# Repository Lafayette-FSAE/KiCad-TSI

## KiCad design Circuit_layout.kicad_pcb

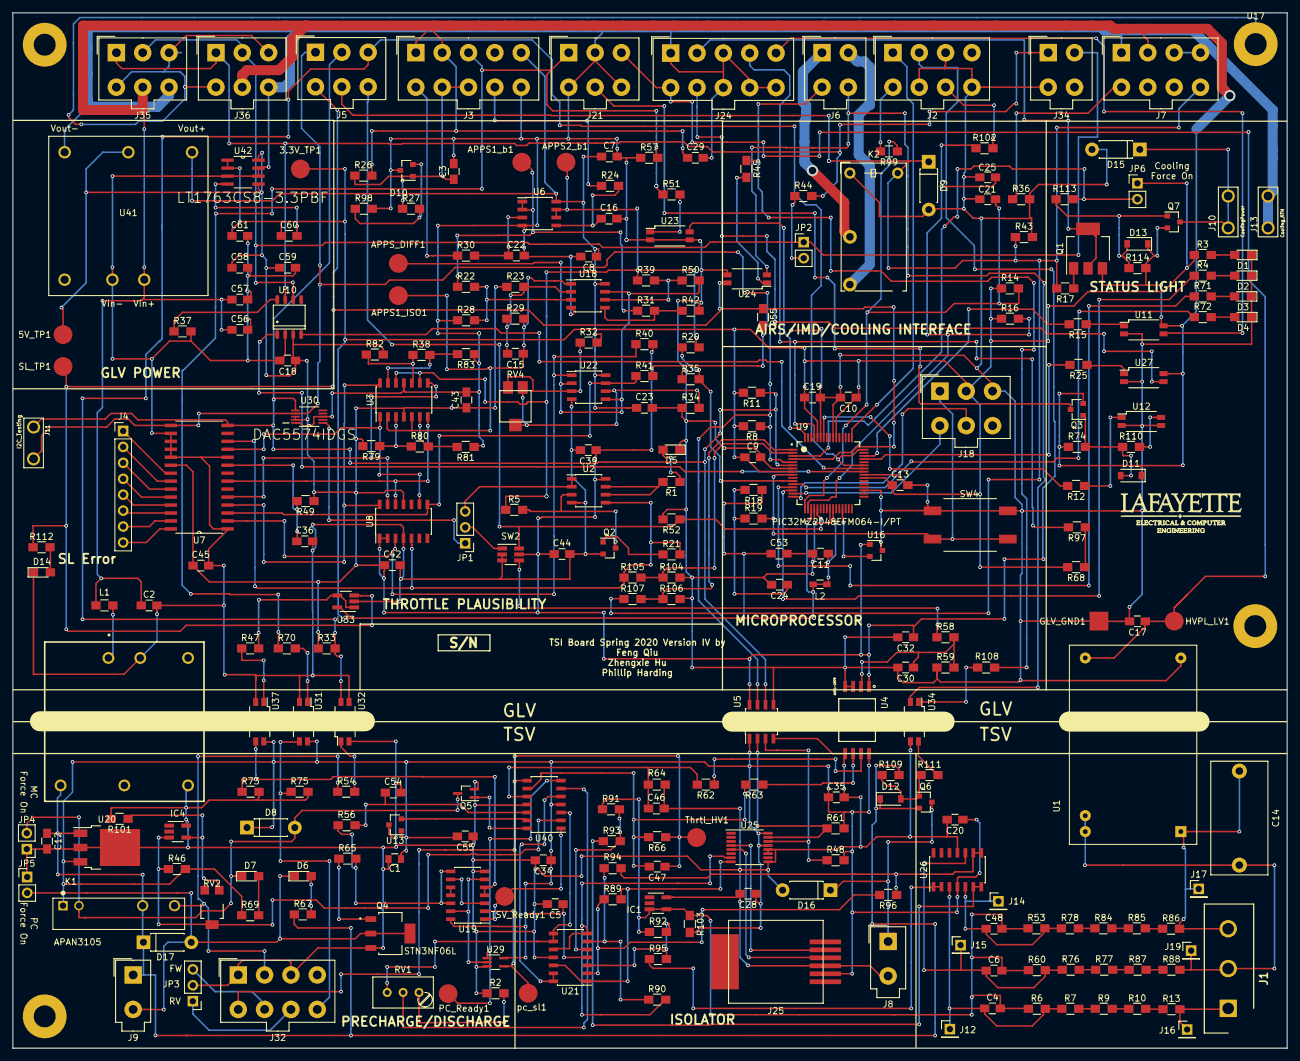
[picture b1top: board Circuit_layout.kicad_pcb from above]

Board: 2 copper layers, 203.2 x 165.1 mm, 281 parts (0 on the bottom side), 185 nets.

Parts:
3.3V_TP1: 3.3V_TP; Measurement_Point_Round-SMD-Pad_Big
5V_TP1: 5V_TP; Measurement_Point_Round-SMD-Pad_Big
APPS1_ISO1: APPS1_ISO; Measurement_Point_Round-SMD-Pad_Big
APPS1_b1: APPS1_b; Measurement_Point_Round-SMD-Pad_Big
APPS2_b1: APPS2_b; Measurement_Point_Round-SMD-Pad_Big
APPS_DIFF1: APPS_DIFF; Measurement_Point_Round-SMD-Pad_Big
C1: 0.47u; C_0805
C2, C17: 4.7u; C_0805_HandSoldering
C3, C5, C7, C8, C9, C10, C11, C13, C15, C16, C18, C19, C20, C21, C22, C23, C25, C28, C29, C32, C34, C35, C39, C42, C43, C44, C45, C53, C55, C58: 0.1u; C_0805_HandSoldering
C4, C6, C30, C46, C47, C48: 100p; C_0805_HandSoldering
C12: 0.33u; C_0805_HandSoldering
C14: 1u; C_Rect_L18.0mm_W9.0mm_P15.00mm_FKS3_FKP3
C24: 0.1uF; C_0805_HandSoldering
C36: 33p; C_0805_HandSoldering
C54: 15u; C_0805_HandSoldering
C56, C57, C61: 10u; C_0805_HandSoldering
C59, C60: 1u; C_0805_HandSoldering
D1: Power; LED_0805_HandSoldering
D2: Heartbeat; LED_0805_HandSoldering
D3: Spare/Fault; LED_0805_HandSoldering
D4: Spare; LED_0805_HandSoldering
D5: Throttle_PL; LED_0805_HandSoldering
D6, D7: LED; LED_0805_HandSoldering
D8, D9, D15, D16, D17: 1N4001; D_DO-41_SOD81_P7.62mm_Horizontal
D10: ATL431; SOT-23_D10_special
D11, D12, D13: MMSZ5231B-7-F; D_SOD-123
D14: SL Error; LED_0805_HandSoldering
GLV_GND1: GLV_GND; Measurement_Point_Square-SMD-Pad_Big
HVPL_LV1: TSAL_LV; Measurement_Point_Round-SMD-Pad_Big
IC1, IC4: TS431ILT; SOT-23-5_HandSoldering
J1: TSV; SHDR3W166P0X635_1X3_2032X762X1422P
J2: CoolingSystem; Molex_MiniFit-JR-5556-08A_2x04x4.20mm_Straight
J3: Pedal; Molex_MiniFit-JR-5556-10A_2x05x4.20mm_Straight
J4: Conn_01x08; Pin_Header_Straight_1x08_Pitch2.54mm
J5: Testing Connector; Molex_MiniFit-JR-5556-06A_2x03x4.20mm_Straight
J6: AIRs/SafetyLoop; Molex_MiniFit-JR-5556-04A_2x02x4.20mm_Straight
J7: IMD; Molex_MiniFit-JR-5556-08A_2x04x4.20mm_Straight
J8: DC_Relay; Molex_MiniFit-JR-5556-02A_2x01x4.20mm_Straight
J9: PC_Relay; Molex_MiniFit-JR-5556-02A_2x01x4.20mm_Straight
J10: CoolingPower; TE_1217861-1
J11: I2C_Testing; TE_1217861-1
J12, J14, J15, J16, J17, J19: Conn_01x01; Pin_Header_Straight_1x01_Pitch2.54mm
J13: Cooling_RTN; TE_1217861-1
J18: ICSP; Molex_MiniFit-JR-5556-06A_2x03x4.20mm_Straight
J21: Lights On Car; Molex_MiniFit-JR-5556-06A_2x03x4.20mm_Straight
J24: Cockpit; Molex_MiniFit-JR-5556-10A_2x05x4.20mm_Straight
J25: RJ11; MOLEX_RJ11
J32: Conn_MC; Molex_MiniFit-JR-5556-08A_2x04x4.20mm_Straight
J34: Can_Iso; Molex_MiniFit-JR-5556-04A_2x02x4.20mm_Straight
J35: GLV_In; Molex_MiniFit-JR-5556-06A_2x03x4.20mm_Straight
J36: GLV_Out; Molex_MiniFit-JR-5556-06A_2x03x4.20mm_Straight
JP1, JP3: Jumper_NC_Dual; Pin_Header_Straight_1x03_Pitch2.54mm
JP2, JP6: Jumper; Pin_Header_Straight_1x02_Pitch2.54mm
JP4, JP5: Jumper-Device; Pin_Header_Straight_1x02_Pitch2.54mm
K1: APAN3105; RELAY_APAN3105
K2: G6B-1174P-US-DC24; Relay_SPST_Finder_32.21-x300_special
L1: 2.2uH; L_0805_HandSoldering
L2: 28nH; L_0603_HandSoldering
PC_Ready1: Precharge_Ready; Measurement_Point_Round-SMD-Pad_Big
PS1: THN_30-2415WI; THN_30
Q1: ZVP0545G; SOT-223-3_TabPin2
Q2: MMBF170; SOT-23
Q3, Q6, Q7: ZVP1320F; SOT-23
Q4: STN3NF06L; SOT230P700X180-4N-speical
Q5: SI1302DL-T1-E3; SOT-323_SC-70_Handsoldering_special
R1, R47, R69, R105, R106: 500; R_0805_HandSoldering
R2: 95k; R_0805_HandSoldering
R3, R4, R71, R72, R112: 330; R_0805_HandSoldering
R5, R6, R8, R11, R14, R16, R17, R18, R21, R22, R23, R28, R29, R31, R39, R40, R41, R42, R48, R50, R52, R53, R59, R60, R61, R62, R63, R68, R89, R90, R91, R92, R93, R94, R95, R96, R97, R101, R110, R111, R113: 10k; R_0805_HandSoldering
R7, R9, R10, R13, R76, R77, R78, R84, R85, R86, R87, R88: 150k; R_0805_HandSoldering
R12, R15, R25: 300; R_0805_HandSoldering
R19, R37, R46, R103, R104: 1k; R_0805_HandSoldering
R20: 2k; R_0805_HandSoldering
R24, R30, R57: 100k; R_0805_HandSoldering
R26: 1K; R_0805_HandSoldering
R27, R98: 10K; R_0805_HandSoldering
R32, R34: 4k; R_0805_HandSoldering
R33, R73, R75: 5k; R_0805_HandSoldering
R35, R107: 3k; R_0805_HandSoldering
R36, R43: 2.2k; R_0805_HandSoldering
R38, R80: 9.31k; R_0805_HandSoldering
R44: 120; R_0805_HandSoldering
R45, R51, R54, R55, R67, R70, R108: 2.4k; R_0805_HandSoldering
R49: 3.9K; R_0805_HandSoldering
R56: 56K; R_0805_HandSoldering
R58: 15k; R_0805_HandSoldering
R64, R66: 24.9k; R_0805_HandSoldering
R65: 5K; R_0805_HandSoldering
R74, R109, R114: 1M; R_0805_HandSoldering
R79, R81, R82, R83: 499; R_0805_HandSoldering
R99, R102: 1.6k; R_0805_HandSoldering
RV1: 3296W-1-103LF; Potentiometer_Trimmer_Bourns_3296W
RV2: POT_TRIM; 23BR10KLFTR
RV4: 1k; trim_pot
SL_TP1: SL_TP; Measurement_Point_Round-SMD-Pad_Big
SW2: TS5A3159-Q1; SOT-23-6_Handsoldering
SW4: SW_PUSH; SW_RACON_8
TSV_Ready1: TSV_Ready; Measurement_Point_Round-SMD-Pad_Big
Thrtl_HV1: Throttle_HV; Measurement_Point_Round-SMD-Pad_Big
U1: RDE03110S12; RDE03110S12_new
U2: MCP6002; SOIC-8_3.9x4.9mm_Pitch1.27mm
U3, U21, U26, U40: MCP6004; SOIC-14_3.9x8.7mm_Pitch1.27mm
U4: ACPL-C870; SOIC127P1150X360-8N
U5: SI8600AB-B-IS; SOIC-8_3.9x4.9mm_Pitch1.27mm
U6, U18: TS912; SOIC-8_3.9x4.9mm_Pitch1.27mm
U7: MCP23016; SOIC127P1030X265-28N
U8: 74ACT11030; SOIC-14_3.9x8.7mm_Pitch1.27mm
U9: PIC32MZ2048EFM064-I/PT; QFP50P1200X1200X120-64N
U10: MCP2551-I/SN; SO-8
U11, U12, U23, U24, U27, U31, U32, U34, U37: TLP293; SOP-4_4.4x2.8mm_Pitch1.27mm
U13: REF3033; SOT-23
U14, U15, U28: Mounting_hole; MountingHole_3.5mm_Pad
U16: MCP9700AT-H/TT; SOT-23
U17: Chassis Ground; MountingHole_3.5mm_Pad
U19: 74HC00; SOIC-14_3.9x8.7mm_Pitch1.27mm
U20: MC7805BDTRKG; TO-252-3_TabPin4
U22: TS372; SOIC-8_3.9x4.9mm_Pitch1.27mm
U25: NCD9830DBR2G; TSSOP-16_4.4x5mm_Pitch0.65mm
U29: SN74LVC1G08DCKR; SOT-353_SC-70-5_Handsoldering
U30: DAC5574IDGS; SOP50P490X110-10N
U33: MCP6001; SOT-23-5_HandSoldering
U41: PDQ10-Q24-D5-D; PDQ_DCDC
U42: LT1763CS8-3.3PBF; SOIC127P600X175-8N
pc_sl1: pc_sl; Measurement_Point_Round-SMD-Pad_Big

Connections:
/+1.24Vref: IC4.3, R46.1, RV2.2, U40.2
/+3.3V: 3.3V_TP1.1, C9.1, C10.1, C11.1, C13.1, C19.1, C53.1, C60.1, C61.1, J18.2, JP6.1, L2.1, L2.2, R3.1, R8.2, R11.2, R14.1, R16.1, R18.1, R68.2, U9.8, U9.19, U9.26, U9.39, U9.54, U9.60, U33.5, U42.1, U42.2
/+5HV: C1.1, C5.1, C20.1, C28.1, C34.1, C35.1, C55.2, D8.1, J25.5, K1.A1, R46.2, R48.2, R61.2, R69.1, R103.2, U4.8, U5.1, U13.1, U19.14, U20.3, U21.4, U25.13, U25.16, U26.4, U29.5, U31.4, U37.4, U40.4
/+5V: 5V_TP1.1, C18.1, C32.1, C39.1, C42.1, C43.1, C44.1, C45.1, C58.1, C59.1, J2.2, R23.1, R33.1, R40.2, R41.2, R49.1, R55.2, R79.2, R82.2, SW2.5, U2.8, U3.4, U4.1, U5.8, U7.20, U8.1, U8.2, U8.11, U10.3, U16.1, U30.8, U30.9, U41.4, U42.5, U42.8
/+10V: C7.1, C8.1, C23.1, J3.5, R32.2, U6.8, U18.8, U22.8, U41.3
/+24V: C2.1, C29.1, C56.1, C57.1, D11.1, D13.1, J3.1, J3.2, J7.2, J35.5, J36.5, L1.1, Q1.3, Q3.2, Q7.2, R26.2, R74.1, R114.2, U11.4, U27.4, U41.1
/AIRs+: J6.3, R45.1, R108.1
/AIRs-: J6.4, U24.2, U34.2
/APPS: R20.1, R35.2, U9.11
/BP: J3.3, J21.1, R51.1, R57.2, R70.1
/BP_RTN: C2.2, C3.2, C7.2, C8.2, C9.2, C10.2, C11.2, C13.2, C16.2, C17.2, C18.2, C19.2, C21.2, C22.2, C23.2, C24.2, C25.2, C29.2, C30.2, C32.2, C36.2, C39.2, C42.2, C43.2, C44.2, C45.2, C53.2, C56.2, C57.2, C58.2, C59.2, C61.2, D1.1, D2.1, D3.1, D4.1, D5.1, D9.2, D10.2, D14.1, D15.2, GLV_GND1.1, J2.3, J2.6, J2.8, J3.10, J7.1, J7.3, J7.4, J13.1, J13.2, J18.3, J21.2, J21.4, J21.6, J24.1, J24.3, J24.8, J24.9, J24.10, J34.3, J35.6, J36.6, K2.A2, PS1.2, Q2.2, R28.1, R34.1, R35.1, R36.2, R37.2, R42.2, R43.2, R52.2, R57.1, R59.1, R81.1, R83.1, R98.2, R104.2, R106.2, SW2.2, SW2.3, SW4.2, U1.12, U2.4, U3.11, U4.3, U4.4, U5.5, U6.4, U7.1, U7.10, U7.16, U7.17, U7.18, U7.19, U8.4, U9.7, U9.20, U9.25, U9.34, U9.35, U9.40, U9.55, U9.59, U10.2, U11.2, U12.2, U12.3, U16.3, U18.4, U22.4, U23.2, U23.3, U24.3, U27.2, U30.3, U30.10, U31.2, U32.3, U33.2, U37.2, U41.2, U41.5, U42.3, U42.6, U42.7
/BP_uC: U9.64, U23.4
/CANRX: U9.42, U10.4
/CANTX: U9.41, U10.1
/CH_gnd: J35.3, J35.4, J36.3, J36.4, U17.1
/CoolTemp_1: C21.1, R14.2, R99.1, U9.17
/CoolTemp_2: C25.1, R16.2, R102.1, U9.18
/CoolTemp_In_1: J2.5, R99.2
/CoolTemp_In_2: J2.7, R102.2
/Cooling_CTRL: JP6.2, R113.2, U9.3
/Cooling_power: D15.1, J10.1, J10.2, Q7.3
/D_LED_CTRL: R15.2, U9.46
/Drive_BTN: J24.4, R97.2, U9.61
/FlowRate: J2.1, U9.49
/GLV Interface/CAN_H: J34.1, J35.1, J36.1, R44.2, U10.7
/GLV Interface/CAN_L: J34.2, J35.2, J36.2, JP2.1, U10.6
/GLV Interface/IMD_MHS: J7.5, R36.1
/GLV Interface/SL1_In: J6.1, K2.11
/GLV Interface/SL1_Out: J6.2, K2.14
/HV+: C14.1, J1.3, J17.1, R86.2, U1.1
/HV-: C14.2, J1.2, J19.1, R88.2, U1.23, U1.24
/Heartbeat: R4.1, U9.14
/I/O_Ground: C1.2, C5.2, C12.2, C20.2, C28.2, C34.2, C35.2, C46.2, C54.2, C55.1, D16.2, IC1.5, IC4.5, J8.2, J25.4, J32.1, J32.3, JP3.2, JP4.1, JP5.1, PS1.5, Q4.3, Q5.3, R2.1, R64.1, R73.2, R75.2, R101.2, U4.5, U5.4, U13.3, U19.7, U20.2, U20.4, U21.11, U25.9, U25.11, U25.12, U26.11, U29.3, U32.2, U34.3, U40.11
/IMD_Status: D9.1, J5.5, J7.8, K2.A1, R17.2, R43.1, R107.1
/IMD_Status_3.3: R106.1, R107.2, U9.1
/Isolators/A1_HV: J25.2, U25.4
/Isolators/A2_HV: J25.3, U25.5
/Isolators/DiffAmpRef: C4.2, C6.2, C48.2, IC1.3, IC1.4, R6.1, R53.1, R60.1, R91.1, R92.1, R103.1
/Isolators/MC+: J1.1, J16.1, R13.2
/Isolators/SCL_HV: R48.1, U5.3, U25.14
/Isolators/SDA_HV: R61.1, U5.2, U25.15
/MC_V: R89.2, U21.1, U21.12, U25.8
/PC_ready: J5.3, R33.2, U9.43, U9.48, U32.4
/PGEC: J18.4, U9.15
/PGED: J18.5, U9.16
/Pre-Charge/+3.3Vref: U13.2, U40.13
/Pre-Charge/+24HV: C12.1, D12.1, D17.1, J9.1, K1.14, PS1.3, Q6.2, R67.1, R109.2, U20.1
/Pre-Charge/BP_HV: J32.8, R75.1, U31.3
/Pre-Charge/DC_Relay+: D16.1, J8.1, Q6.3
/Pre-Charge/IGNI_VCC: J32.2, K1.11, R54.1
/Pre-Charge/PC_Relay-: D6.1, D17.2, J9.2, JP5.2, Q4.1, Q4.4
/Pre-Charge/Precharge_Ready: PC_Ready1.1, U29.1, U40.7
/Pre-Charge/Safety_Loop_HV: R73.1, U19.4, U19.5, U37.3
/Pre-Charge/TSV_Ready: TSV_Ready1.1, U19.1, U40.1
/Pre-Charge/pc_and_sl_ready: U19.2, U29.4, pc_sl1.1
/RTDS_CTRL: R12.2, U9.58
/SCL: J5.2, J11.1, R11.1, U5.6, U7.14, U9.6, U30.6
/SDA: J5.1, J11.2, R8.1, U5.7, U7.15, U9.5, U30.7
/SPARE_LED_CTRL: R25.2, U9.45
/Safety_Loop: J5.4, R55.1, R112.1, SL_TP1.1, U9.4, U24.4, U33.3
/Spare_Blue: R72.1, U9.12
/Spare_Red: R71.1, U9.13
/Status Lights/Drive_LED: J24.5, U11.3
/Status Lights/IMD_Fault_LED: J24.2, Q1.2
/Status Lights/RTDS: J21.5, Q3.3
/Status Lights/SPARE_LED: J24.7, U27.3
/Status Lights/TSAL_1: C17.1, HVPL_LV1.1, J21.3, J24.6, U1.13
/TSV_V: R90.2, U21.7, U21.10, U25.7
/ThrottlePlausibility/5v_ref: C3.1, D10.3, J3.7, J3.8, R26.1, R27.1
/ThrottlePlausibility/APPS1: J3.6, R30.1
/ThrottlePlausibility/APPS1_ISO: APPS1_ISO1.1, C15.1, R29.2, U3.2, U3.5, U18.1
/ThrottlePlausibility/APPS1_b: APPS1_b1.1, R22.1, R31.1, U6.1, U6.2
/ThrottlePlausibility/APPS2: J3.9, R24.1
/ThrottlePlausibility/APPS2_b: APPS2_b1.1, R5.1, R20.2, R39.1, U3.9, U3.12, U6.6, U6.7
/ThrottlePlausibility/Pedal_Out: JP1.3, U2.1, U2.2
/Throttle_HV: C47.1, J32.5, R66.1, Thrtl_HV1.1, U40.8
/Throttle_LV: R58.1, SW2.4
/Throttle_PL: R21.2, R105.1, U2.5, U7.12, U8.5
/Throttle_PL_3.3: R104.1, R105.2, U9.2
/Throttle_SEL: J5.6, R52.1, SW2.6, U9.21
/~MCLR: J18.1, R19.2, SW4.1, U9.9
unnamed: APPS_DIFF1.1, R50.2, U18.7, U22.2, U22.5
unnamed: C4.1, J12.1, R6.2, R7.1, U26.3
unnamed: C6.1, J15.1, R60.2, R76.1, U26.10
unnamed: C15.2, R23.2, R29.1, U18.2
unnamed: C16.1, R24.2, U6.5
unnamed: C22.1, R30.2, U6.3
unnamed: C24.1, R18.2, R19.1
unnamed: C30.1, R58.2, R59.2, U4.2
unnamed: C36.1, R49.2, U7.9
unnamed: C46.1, R62.2, R64.2, U40.10
unnamed: C47.2, R63.2, R66.2, U40.9
unnamed: C48.1, J14.1, R53.2, R78.1, U26.5
unnamed: C54.1, R56.2, U40.12
unnamed: C60.2, U42.4
unnamed: D1.2, R3.2
unnamed: D2.2, R4.2
unnamed: D3.2, R71.2
unnamed: D4.2, R72.2
unnamed: D5.2, R1.1
unnamed: D6.2, R67.2
unnamed: D7.1, D8.2, JP4.2, K1.A2, Q5.1
unnamed: D7.2, R69.2
unnamed: D10.1, R27.2, R98.1
unnamed: D11.2, Q3.1, R74.2, R110.1
unnamed: D12.2, Q6.1, R109.1, R111.1
unnamed: D13.2, Q7.1, R113.1, R114.1
unnamed: D14.2, R112.2
unnamed: IC4.4, R101.1, RV2.1
unnamed: J4.1, U7.21
unnamed: J4.2, U7.22
unnamed: J4.3, U7.23
unnamed: J4.4, U7.24
unnamed: J4.5, U7.25
unnamed: J4.6, U7.26
unnamed: J4.7, U7.27
unnamed: J4.8, U7.28
unnamed: J32.6, JP3.3
unnamed: J32.7, JP3.1
unnamed: JP1.1, U30.1
unnamed: JP1.2, SW2.1
unnamed: JP2.2, R44.1
unnamed: L1.2, PS1.1
unnamed: Q1.1, R17.1
unnamed: Q2.1, R21.1
unnamed: Q2.3, R5.2, U2.3
unnamed: Q4.2, R65.1
unnamed: Q5.2, U40.14
unnamed: R1.2, U2.6, U2.7
unnamed: R2.2, RV1.1
unnamed: R7.2, R9.1
unnamed: R9.2, R10.1
unnamed: R10.2, R13.1
unnamed: R12.1, U12.1
unnamed: R15.1, U11.1
unnamed: R22.2, R28.2, U18.3
unnamed: R25.1, U27.1
unnamed: R31.2, R42.1, U18.5
unnamed: R32.1, RV4.1, U22.3
unnamed: R34.2, RV4.2, RV4.3, U22.6
unnamed: R37.1, U10.8
unnamed: R38.1, R82.1, U3.10
unnamed: R38.2, R83.2, U3.13
unnamed: R39.2, R50.1, U18.6
unnamed: R40.1, U7.2, U8.3, U22.1
unnamed: R41.1, U7.3, U8.8, U22.7
unnamed: R45.2, U24.1
unnamed: R47.1, U37.1
unnamed: R47.2, U33.1, U33.4
unnamed: R51.2, U23.1
unnamed: R54.2, U32.1
unnamed: R56.1, R65.2, U19.8, U19.12
unnamed: R62.1, U4.7
unnamed: R63.1, U4.6
unnamed: R68.1, R97.1
unnamed: R70.2, U31.1
unnamed: R76.2, R77.1
unnamed: R77.2, R87.1
unnamed: R78.2, R84.1
unnamed: R79.1, R80.1, U3.3
unnamed: R80.2, R81.2, U3.6
unnamed: R84.2, R85.1
unnamed: R85.2, R86.1
unnamed: R87.2, R88.1
unnamed: R89.1, R96.2, U21.2
unnamed: R90.1, R94.2, U21.6
unnamed: R91.2, R93.2, U21.5
unnamed: R92.2, R95.2, U21.3
unnamed: R93.1, U26.6, U26.7
unnamed: R94.1, R96.1, U26.8, U26.9
unnamed: R95.1, U26.1, U26.2
unnamed: R108.2, U34.1
unnamed: R110.2, U12.4
unnamed: R111.2, U34.4
unnamed: RV1.2, U40.6
unnamed: RV1.3, U21.8, U21.9, U40.3
unnamed: U3.1, U7.11, U8.9
unnamed: U3.7, U7.7, U8.12
unnamed: U3.8, U7.5, U8.13
unnamed: U3.14, U7.4, U8.14
unnamed: U9.29, U16.2
unnamed: U19.3, U19.9
unnamed: U19.10, U19.11
unnamed: U19.6, U19.13, U29.2
unnamed: U21.13, U21.14, U40.5

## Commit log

2019-09-18 back up from 2018
2019-09-18 kicad mod backup
2019-09-23 F2018 version 1 before review
2019-09-24 backup; Add cooling power connector
2019-09-29 modify cooling power
    relay added for cooling power control; reroute signals to PIC32 analog input
2019-10-03 Version 3 ready for FREEDFM check
2019-10-07 Additional spade connector for Cooling_RTN
    Ready for fabrication
2019-10-17 fixing Vref on diff amps
2019-12-11 v3.1
2020-02-18 TSI v4.1
